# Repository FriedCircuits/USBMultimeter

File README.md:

USB Multimeter
===============================================

This repo will contain all the design and firmware code for the USB Multimeter as development progresses.

Currently the project is just a add-on board for the STM32F429 Discovery board. See the subfolder for details. 

More information at
[https://hackaday.io/friedcircuits](https://hackaday.io/friedcircuits)

License: All source code and designs are released under 

Creative Commons ShareAlike 

CC BY-SA

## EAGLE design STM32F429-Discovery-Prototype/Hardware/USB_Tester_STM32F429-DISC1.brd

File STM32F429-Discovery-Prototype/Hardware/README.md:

Hardware for USB Multimeter STM32F429 Add-on Board
======================================================

Warning: The TX/RX pairs need to be swapped for this design to work.

I only made one spin of this board and ended up swapping the pairs with some bodge wires.

Also there is an I2C address conflict with the INA219's. I forgot to set the 2nd one to another address.

This is here just as a referance as this was a one off board.

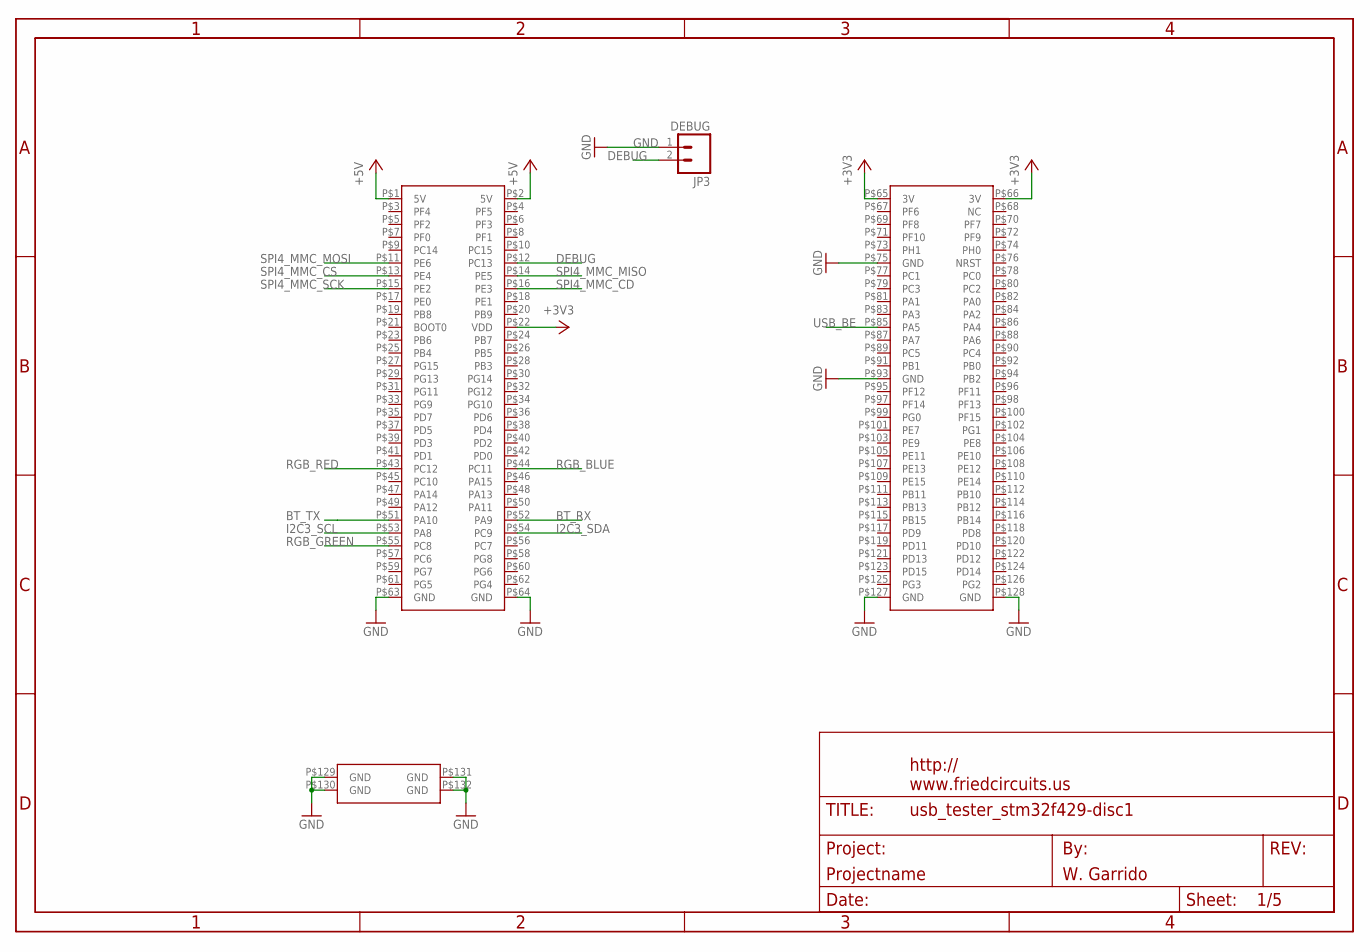
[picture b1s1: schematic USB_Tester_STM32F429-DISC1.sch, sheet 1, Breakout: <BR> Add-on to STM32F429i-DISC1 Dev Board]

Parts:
JP3: DEBUG; 1X02_LOCK
U$1: STM32F429-DISCO
U$3: FRAME_DINA4_L; FC_CREDIT

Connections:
+3V3: U$1.P$22 (VDD), U$1.P$65 (3V), U$1.P$66 (3V); also elsewhere on the board
+5V: U$1.P$1 (5V), U$1.P$2 (5V); also elsewhere on the board
BT_RX: U$1.P$52 (PA9); also elsewhere on the board
BT_TX: U$1.P$51 (PA10); also elsewhere on the board
DEBUG: JP3.2, U$1.P$12 (PC13)
GND: JP3.1, U$1.P$63 (GND), U$1.P$64 (GND), U$1.P$75 (GND), U$1.P$93 (GND), U$1.P$127 (GND), U$1.P$128 (GND), U$1.P$129 (GND), U$1.P$130 (GND), U$1.P$131 (GND), U$1.P$132 (GND); also elsewhere on the board
I2C3_SCL: U$1.P$53 (PA8); also elsewhere on the board
I2C3_SDA: U$1.P$54 (PC9); also elsewhere on the board
RGB_BLUE: U$1.P$44 (PC11); also elsewhere on the board
RGB_GREEN: U$1.P$55 (PC8); also elsewhere on the board
RGB_RED: U$1.P$43 (PC12); also elsewhere on the board
SPI4_MMC_CD: U$1.P$16 (PE3); also elsewhere on the board
SPI4_MMC_CS: U$1.P$13 (PE4); also elsewhere on the board
SPI4_MMC_MISO: U$1.P$14 (PE5); also elsewhere on the board
SPI4_MMC_MOSI: U$1.P$11 (PE6); also elsewhere on the board
SPI4_MMC_SCK: U$1.P$15 (PE2); also elsewhere on the board
USB_BE: U$1.P$85 (PA5); also elsewhere on the board

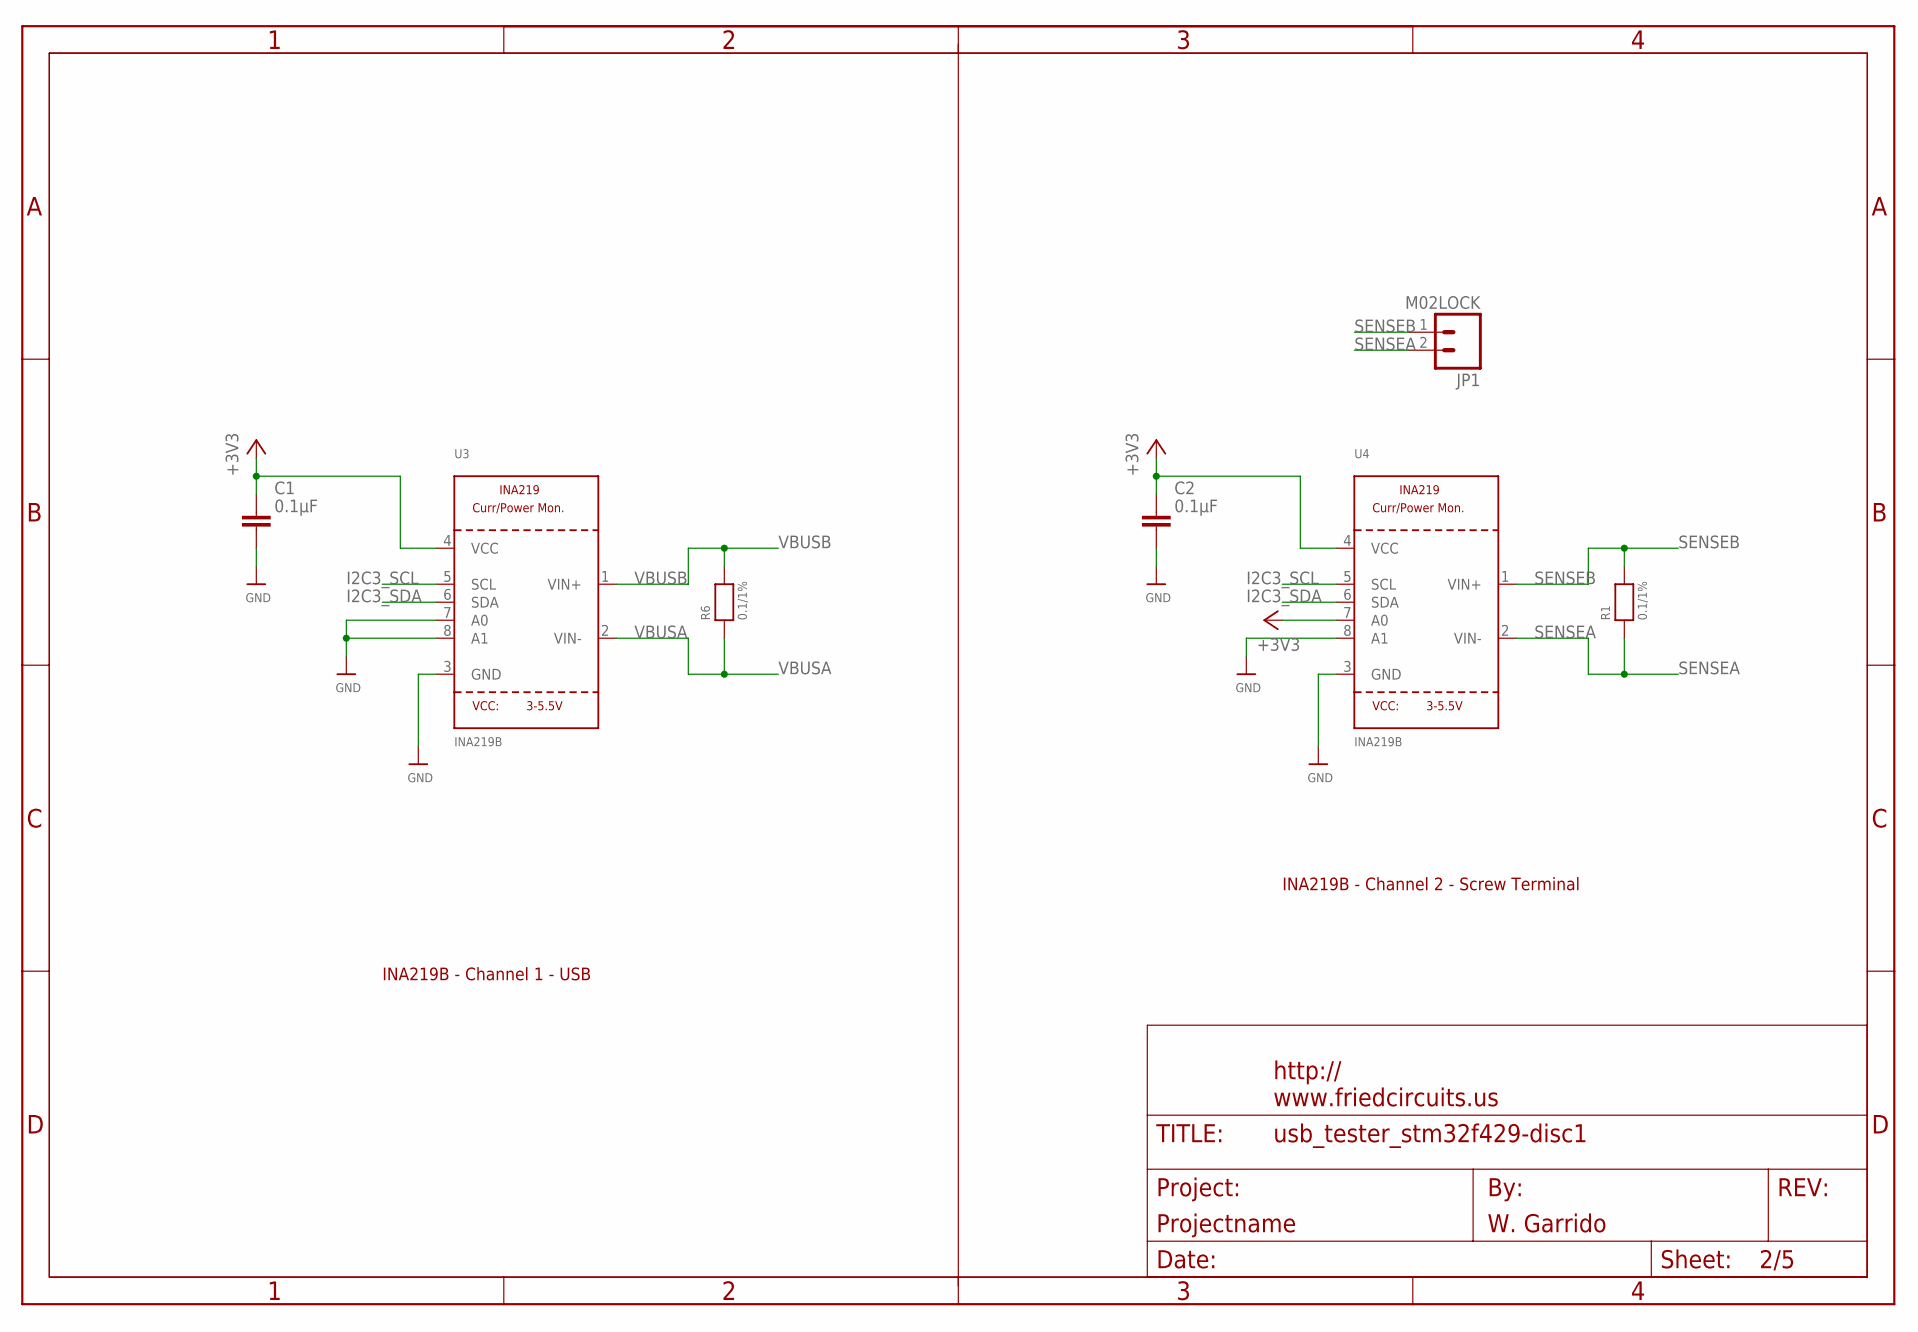
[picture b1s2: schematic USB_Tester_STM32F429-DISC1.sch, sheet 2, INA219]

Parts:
C1, C2: 0.1µF; C603
JP1: M02LOCK; 1X02_LOCK
R1, R6: 0.1/1%; 2512
U3, U4: INA219B; SOT23-8
U$4: FRAME_DINA4_L; FC_CREDIT

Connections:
+3V3: C1.1, C2.1, U3.4 (VCC), U4.4 (VCC), U4.7 (A0); also elsewhere on the board
GND: C1.2, C2.2, U3.3 (GND), U3.7 (A0), U3.8 (A1), U4.3 (GND), U4.8 (A1); also elsewhere on the board
I2C3_SCL: U3.5 (SCL), U4.5 (SCL); also elsewhere on the board
I2C3_SDA: U3.6 (SDA), U4.6 (SDA); also elsewhere on the board
SENSEA: JP1.2, R1.1, U4.2 (VIN-); also elsewhere on the board
SENSEB: JP1.1, R1.2, U4.1 (VIN+); also elsewhere on the board
VBUSA: R6.1, U3.2 (VIN-); also elsewhere on the board
VBUSB: R6.2, U3.1 (VIN+); also elsewhere on the board

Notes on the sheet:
INA219B - Channel 1 - USB
INA219B - Channel 2 - Screw Terminal

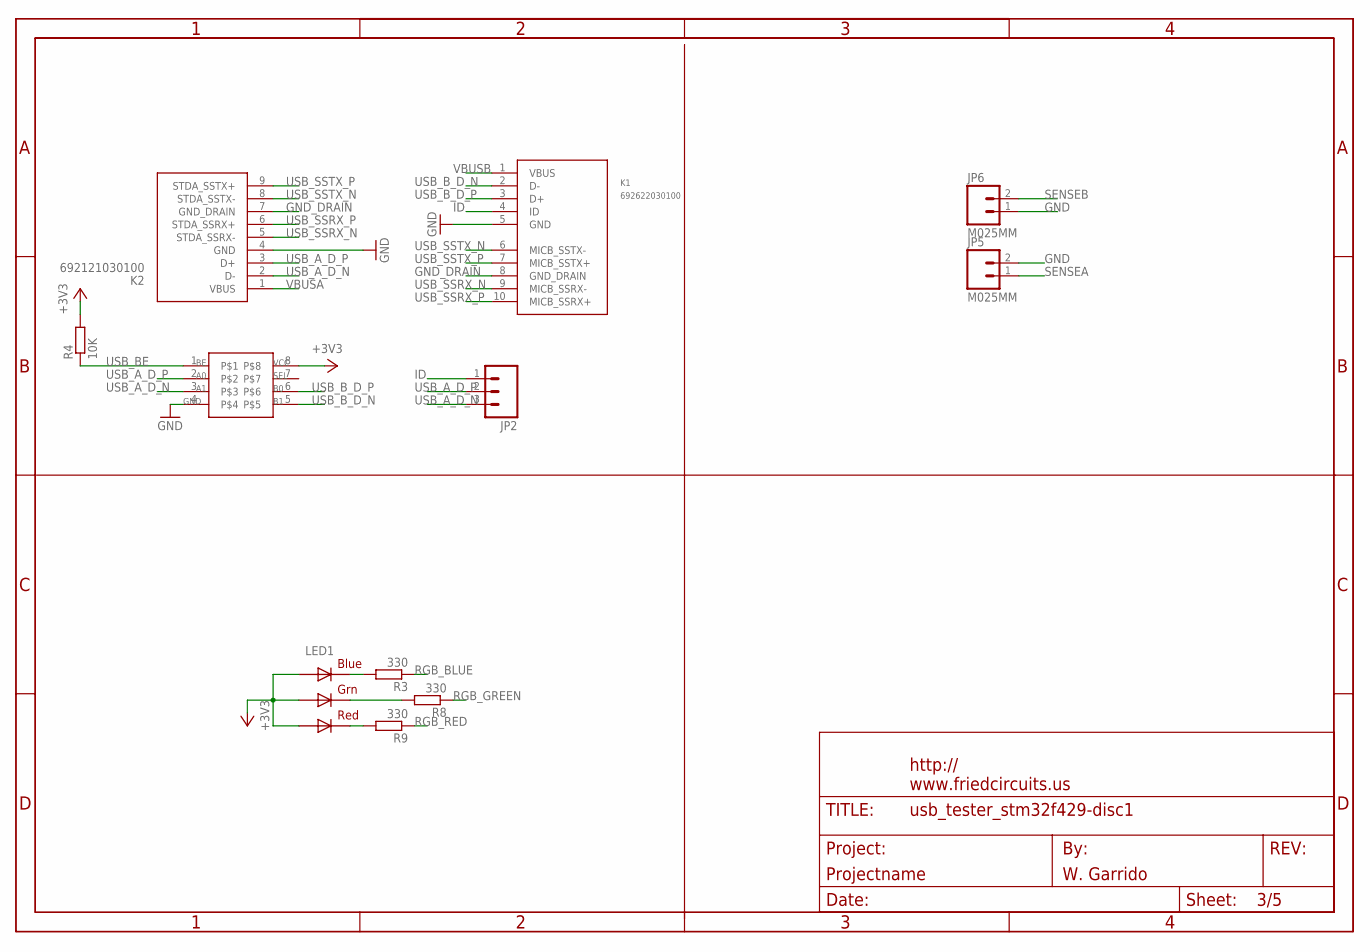
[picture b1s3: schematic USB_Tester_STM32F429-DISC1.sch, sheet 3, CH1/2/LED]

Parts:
JP2: M03LOCK; 1X03_LOCK
JP5, JP6: M025MM; SCREWTERMINAL-5MM-2
K1: 692622030100
K2: 692121030100
LED1: RGBLED5050
R3, R8, R9: 330; R603
R4: 10K; R603
U$2: FRAME_DINA4_L; FC_CREDIT
U$17: ADG3242; SOT23-8

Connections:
+3V3: LED1.1 (GREEN_A), LED1.2 (RED_A), LED1.3 (BLUE_A), R4.2, U$17.8; also elsewhere on the board
GND: JP5.2, JP6.1, K1.5 (GND), K2.4 (GND), U$17.4; also elsewhere on the board
GND_DRAIN: K1.8 (GND_DRAIN), K2.7 (GND_DRAIN)
ID: JP2.1, K1.4 (ID)
unnamed: LED1.4 (BLUE_C), R3.2
unnamed: LED1.6 (GREEN_C), R8.2
unnamed: LED1.5 (RED_C), R9.2
RGB_BLUE: R3.1; also elsewhere on the board
RGB_GREEN: R8.1; also elsewhere on the board
RGB_RED: R9.1; also elsewhere on the board
SENSEA: JP5.1; also elsewhere on the board
SENSEB: JP6.2; also elsewhere on the board
USB_A_D_N: JP2.3, K2.2 (D-), U$17.3
USB_A_D_P: JP2.2, K2.3 (D+), U$17.2
USB_BE: R4.1, U$17.1; also elsewhere on the board
USB_B_D_N: K1.2 (D-), U$17.5
USB_B_D_P: K1.3 (D+), U$17.6
USB_SSRX_N: K1.9 (MICB_SSRX-), K2.5 (STDA_SSRX-)
USB_SSRX_P: K1.10 (MICB_SSRX+), K2.6 (STDA_SSRX+)
USB_SSTX_N: K1.6 (MICB_SSTX-), K2.8 (STDA_SSTX-)
USB_SSTX_P: K1.7 (MICB_SSTX+), K2.9 (STDA_SSTX+)
VBUSA: K2.1 (VBUS); also elsewhere on the board
VBUSB: K1.1 (VBUS); also elsewhere on the board

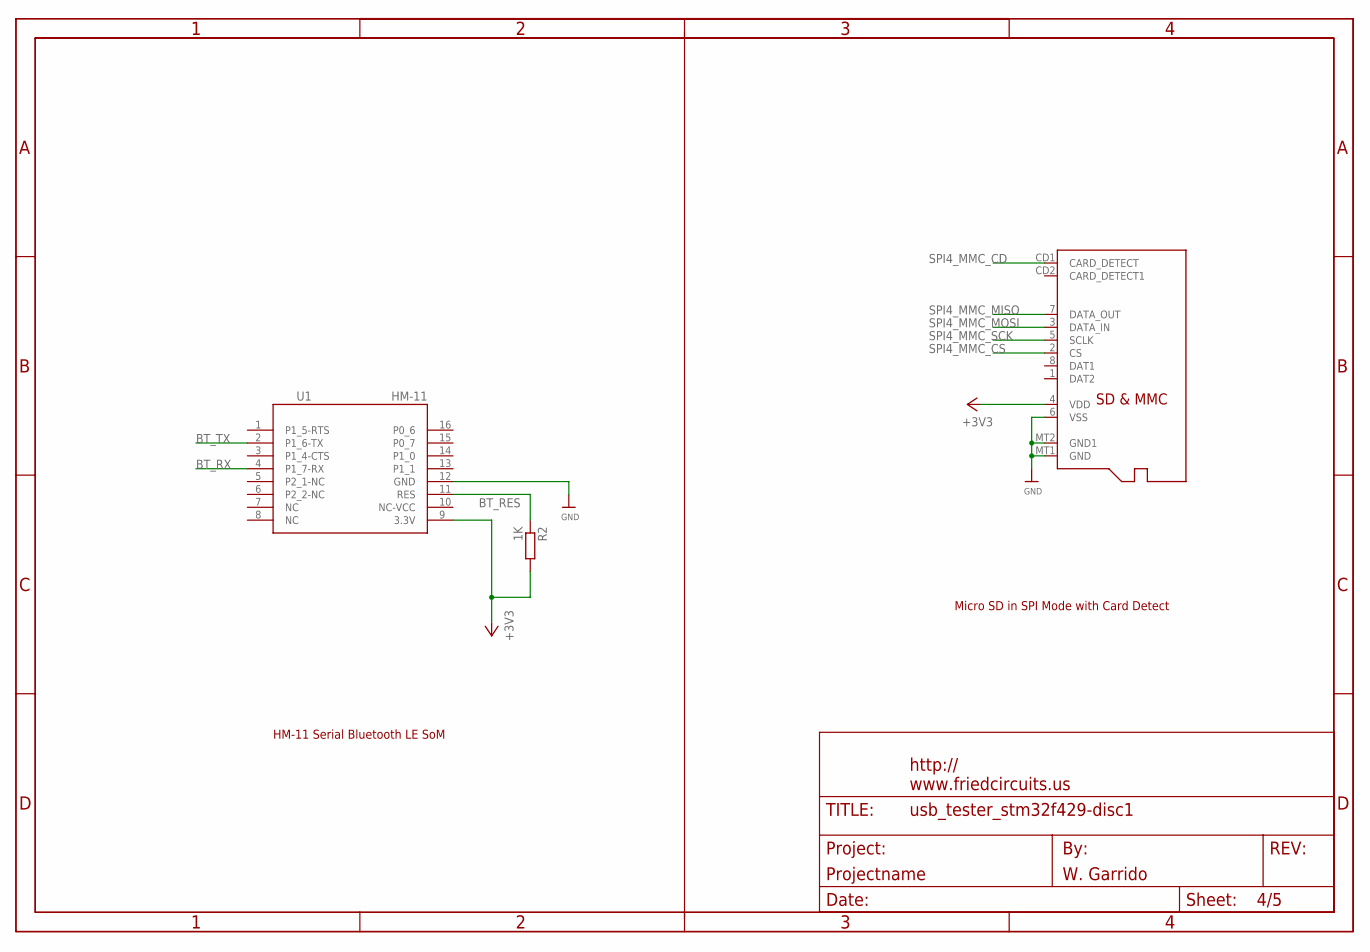
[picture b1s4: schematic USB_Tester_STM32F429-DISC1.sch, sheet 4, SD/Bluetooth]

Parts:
R2: 1K; R603
SD_CARD1: MICROSD
U1: HM-11
U$5: FRAME_DINA4_L; FC_CREDIT

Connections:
+3V3: R2.2, SD_CARD1.4 (VDD), U1.9 (3.3V); also elsewhere on the board
BT_RES: R2.1, U1.11 (RES)
BT_RX: U1.4 (P1_7-RX); also elsewhere on the board
BT_TX: U1.2 (P1_6-TX); also elsewhere on the board
GND: SD_CARD1.6 (VSS), SD_CARD1.MT1 (GND), SD_CARD1.MT2 (GND1), U1.12 (GND); also elsewhere on the board
SPI4_MMC_CD: SD_CARD1.CD1 (CARD_DETECT); also elsewhere on the board
SPI4_MMC_CS: SD_CARD1.2 (CS); also elsewhere on the board
SPI4_MMC_MISO: SD_CARD1.7 (DATA_OUT); also elsewhere on the board
SPI4_MMC_MOSI: SD_CARD1.3 (DATA_IN); also elsewhere on the board
SPI4_MMC_SCK: SD_CARD1.5 (SCLK); also elsewhere on the board

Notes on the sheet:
HM-11 Serial Bluetooth LE SoM
Micro SD in SPI Mode with Card Detect

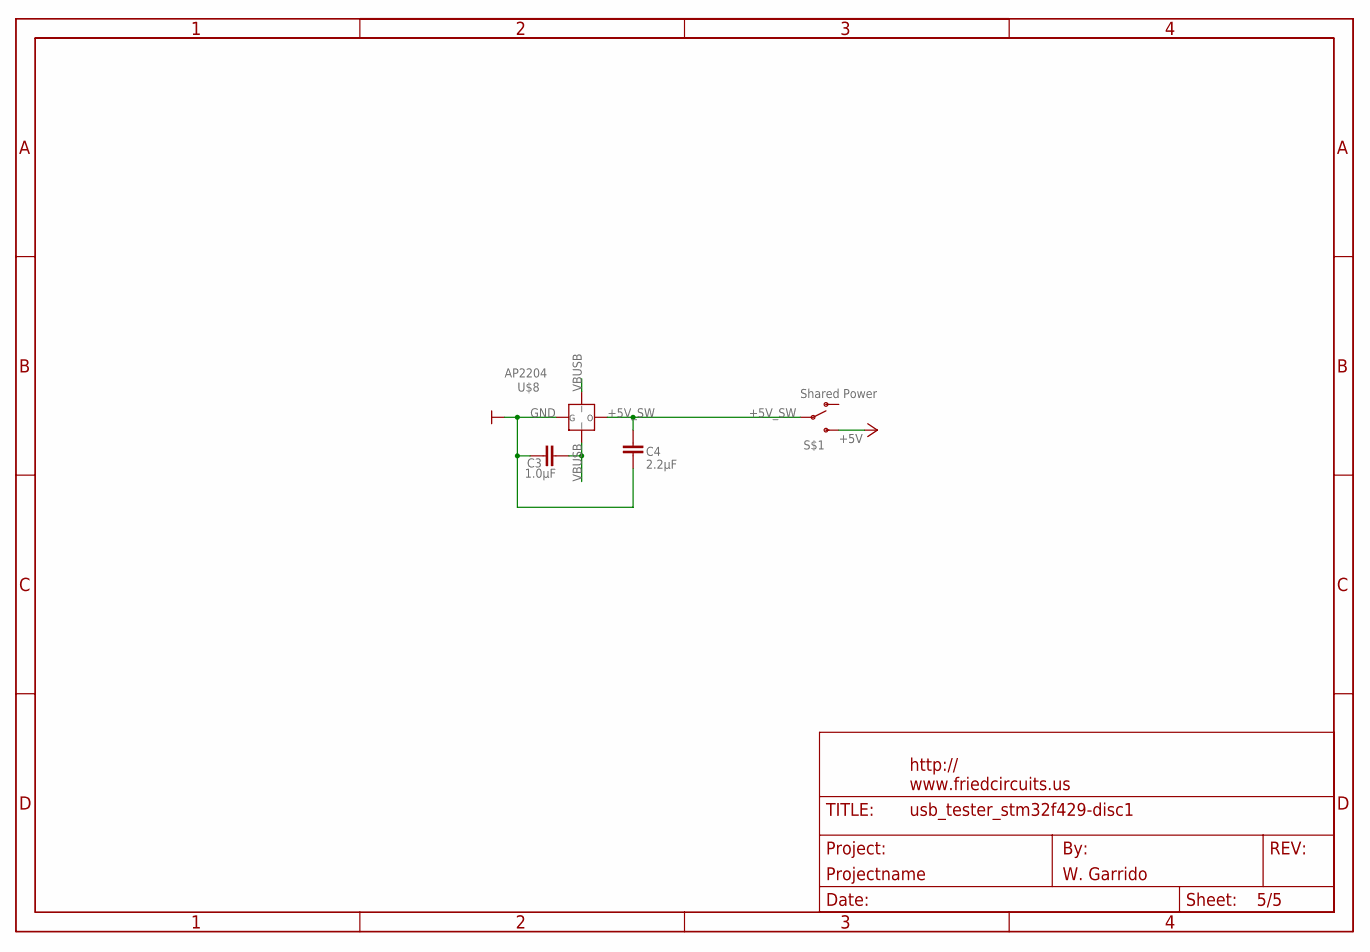
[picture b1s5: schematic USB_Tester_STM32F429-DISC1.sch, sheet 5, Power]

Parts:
C3: 1.0µF; C603
C4: 2.2µF; C603
S$1: Shared Power; KPS-1290
U$6: FRAME_DINA4_L; FC_CREDIT
U$8: AP2204; SOT89-3

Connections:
+5V: S$1.S; also elsewhere on the board
+5V_SW: C4.1, S$1.P, U$8.3 (O)
GND: C3.2, C4.2, U$8.1 (G); also elsewhere on the board
VBUSB: C3.1, U$8.2 (VIN), U$8.4 (VIN); also elsewhere on the board

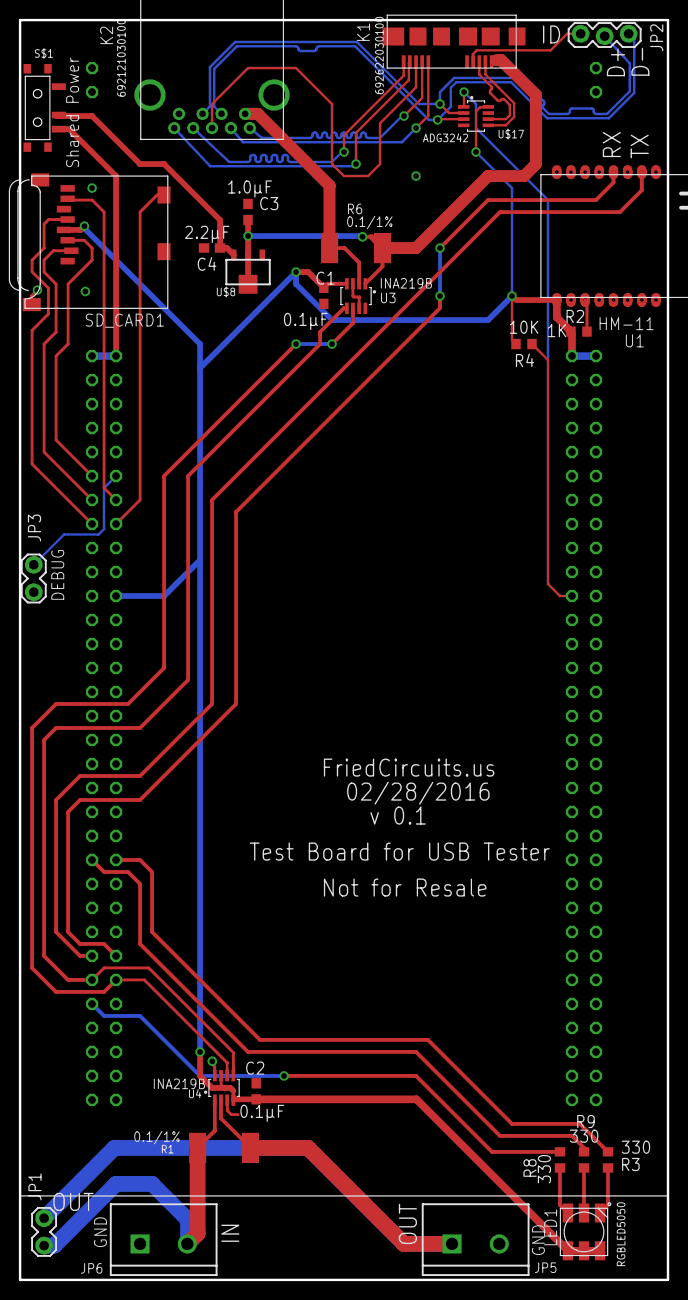
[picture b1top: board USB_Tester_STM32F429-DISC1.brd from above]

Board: 2 copper layers, 68.6 x 133.3 mm, 32 parts (0 on the bottom side), 36 nets.

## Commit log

2016-04-23 Setup structure
2016-04-23 Added hardware eagle and images files
2016-04-23 Alpha code for firmware
2017-03-25 Initial BSP
    For testing only.
2017-03-25 Update BSP URL
2017-03-25 Format fix
2017-03-25 Update file size

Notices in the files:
README.md:
CC BY-NC-SA
parts and their libraries:
SparkFun-Connectors: Licensing: CC v3.0 Share-Alike You are welcome to use this library for commercial purposes.
Wuerth_Elektronik_eiCan_Communication_Co: Copyright: Würth Elektronik
